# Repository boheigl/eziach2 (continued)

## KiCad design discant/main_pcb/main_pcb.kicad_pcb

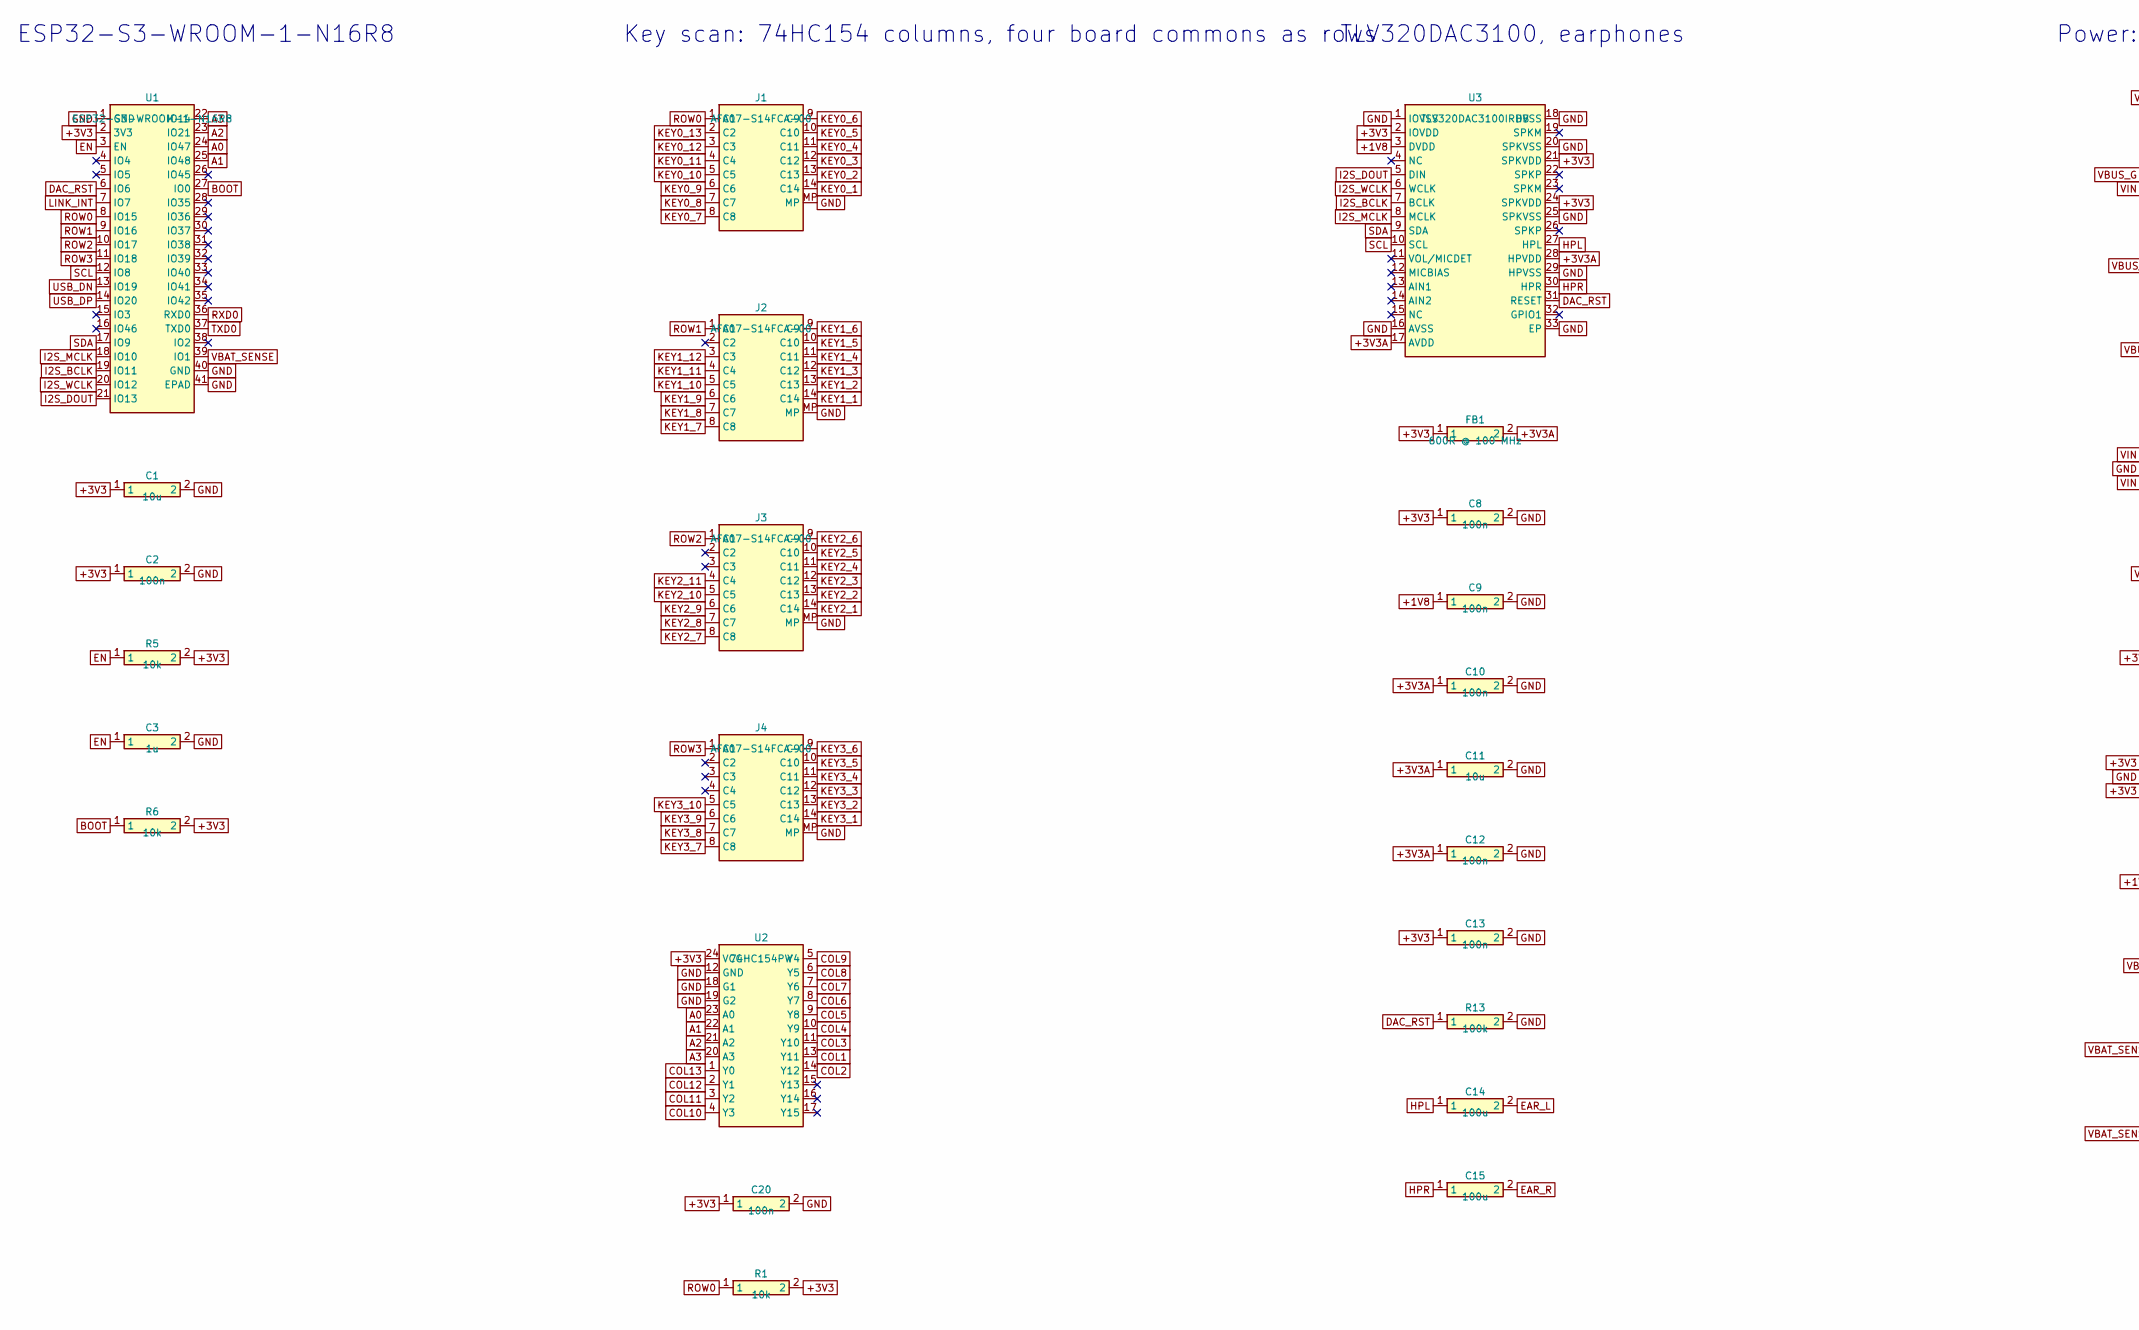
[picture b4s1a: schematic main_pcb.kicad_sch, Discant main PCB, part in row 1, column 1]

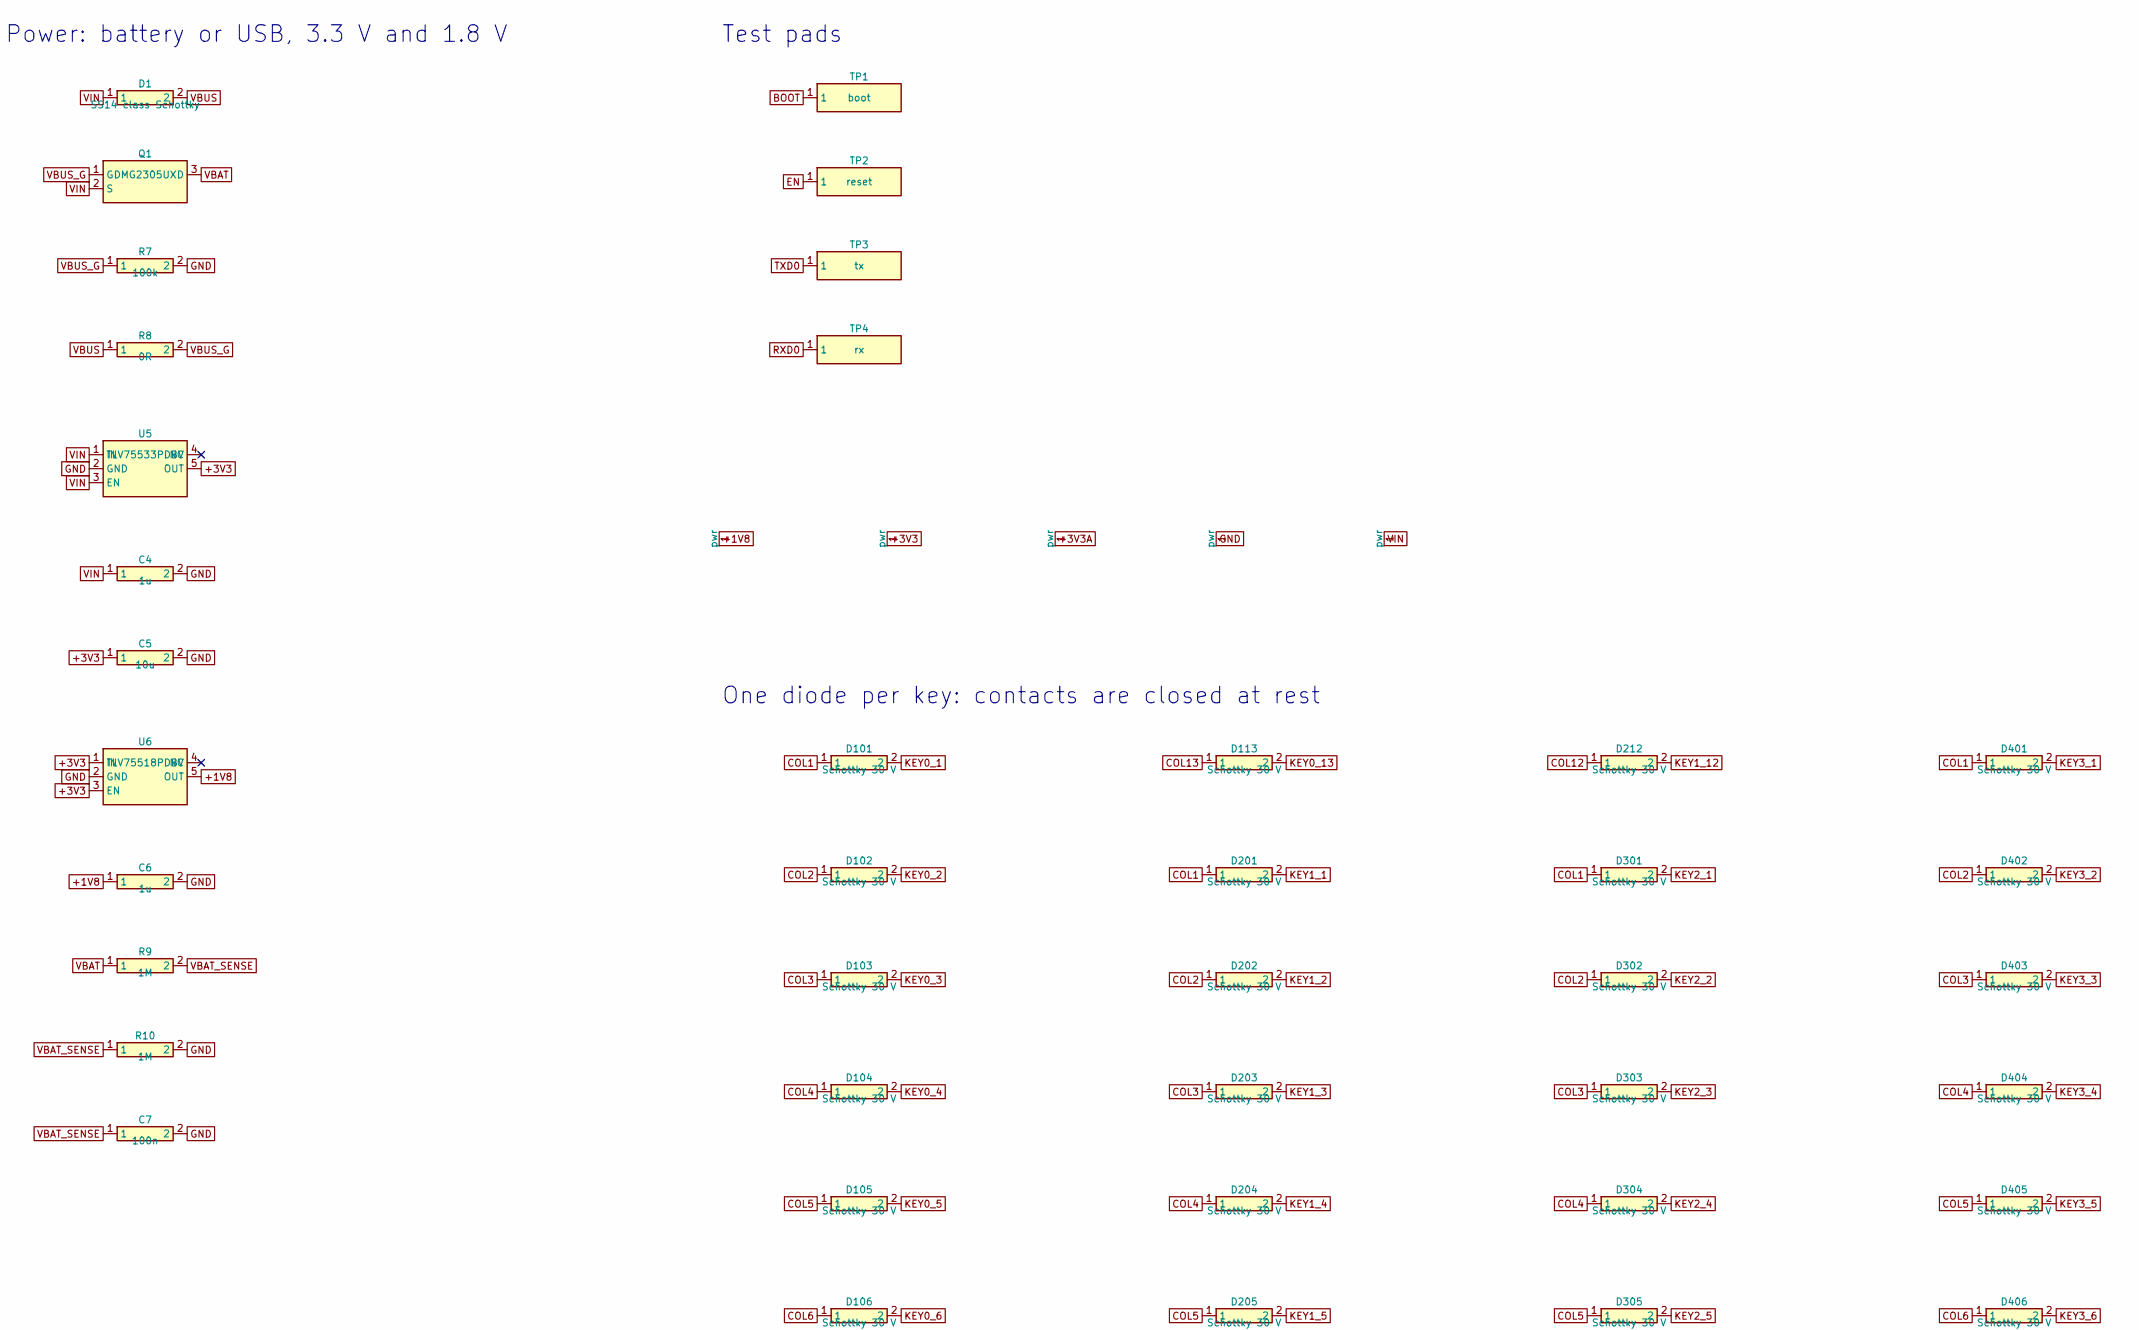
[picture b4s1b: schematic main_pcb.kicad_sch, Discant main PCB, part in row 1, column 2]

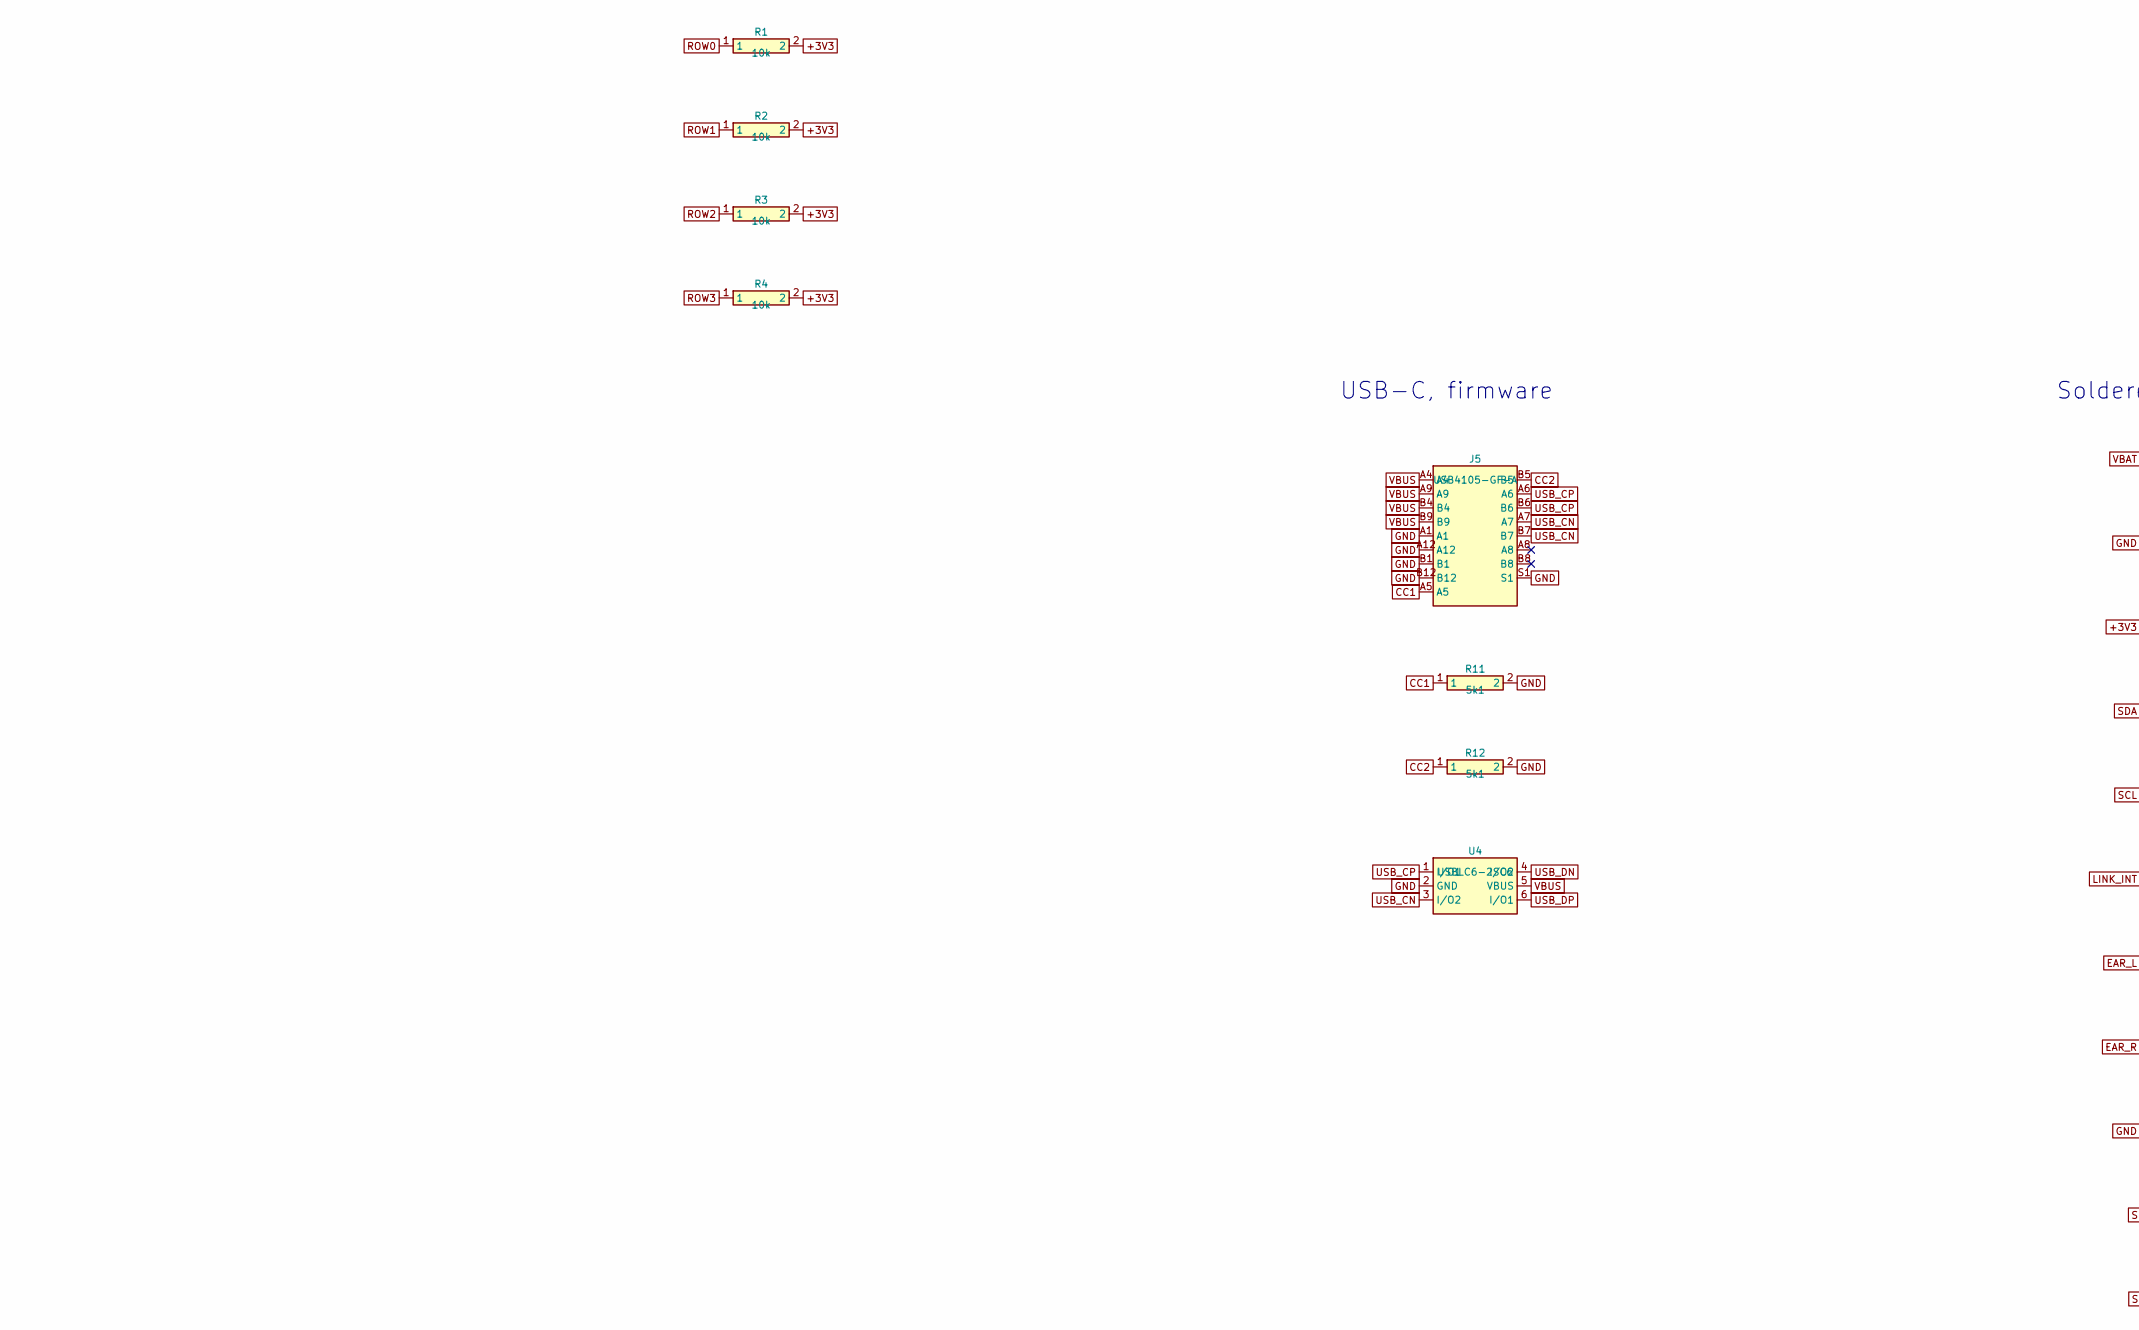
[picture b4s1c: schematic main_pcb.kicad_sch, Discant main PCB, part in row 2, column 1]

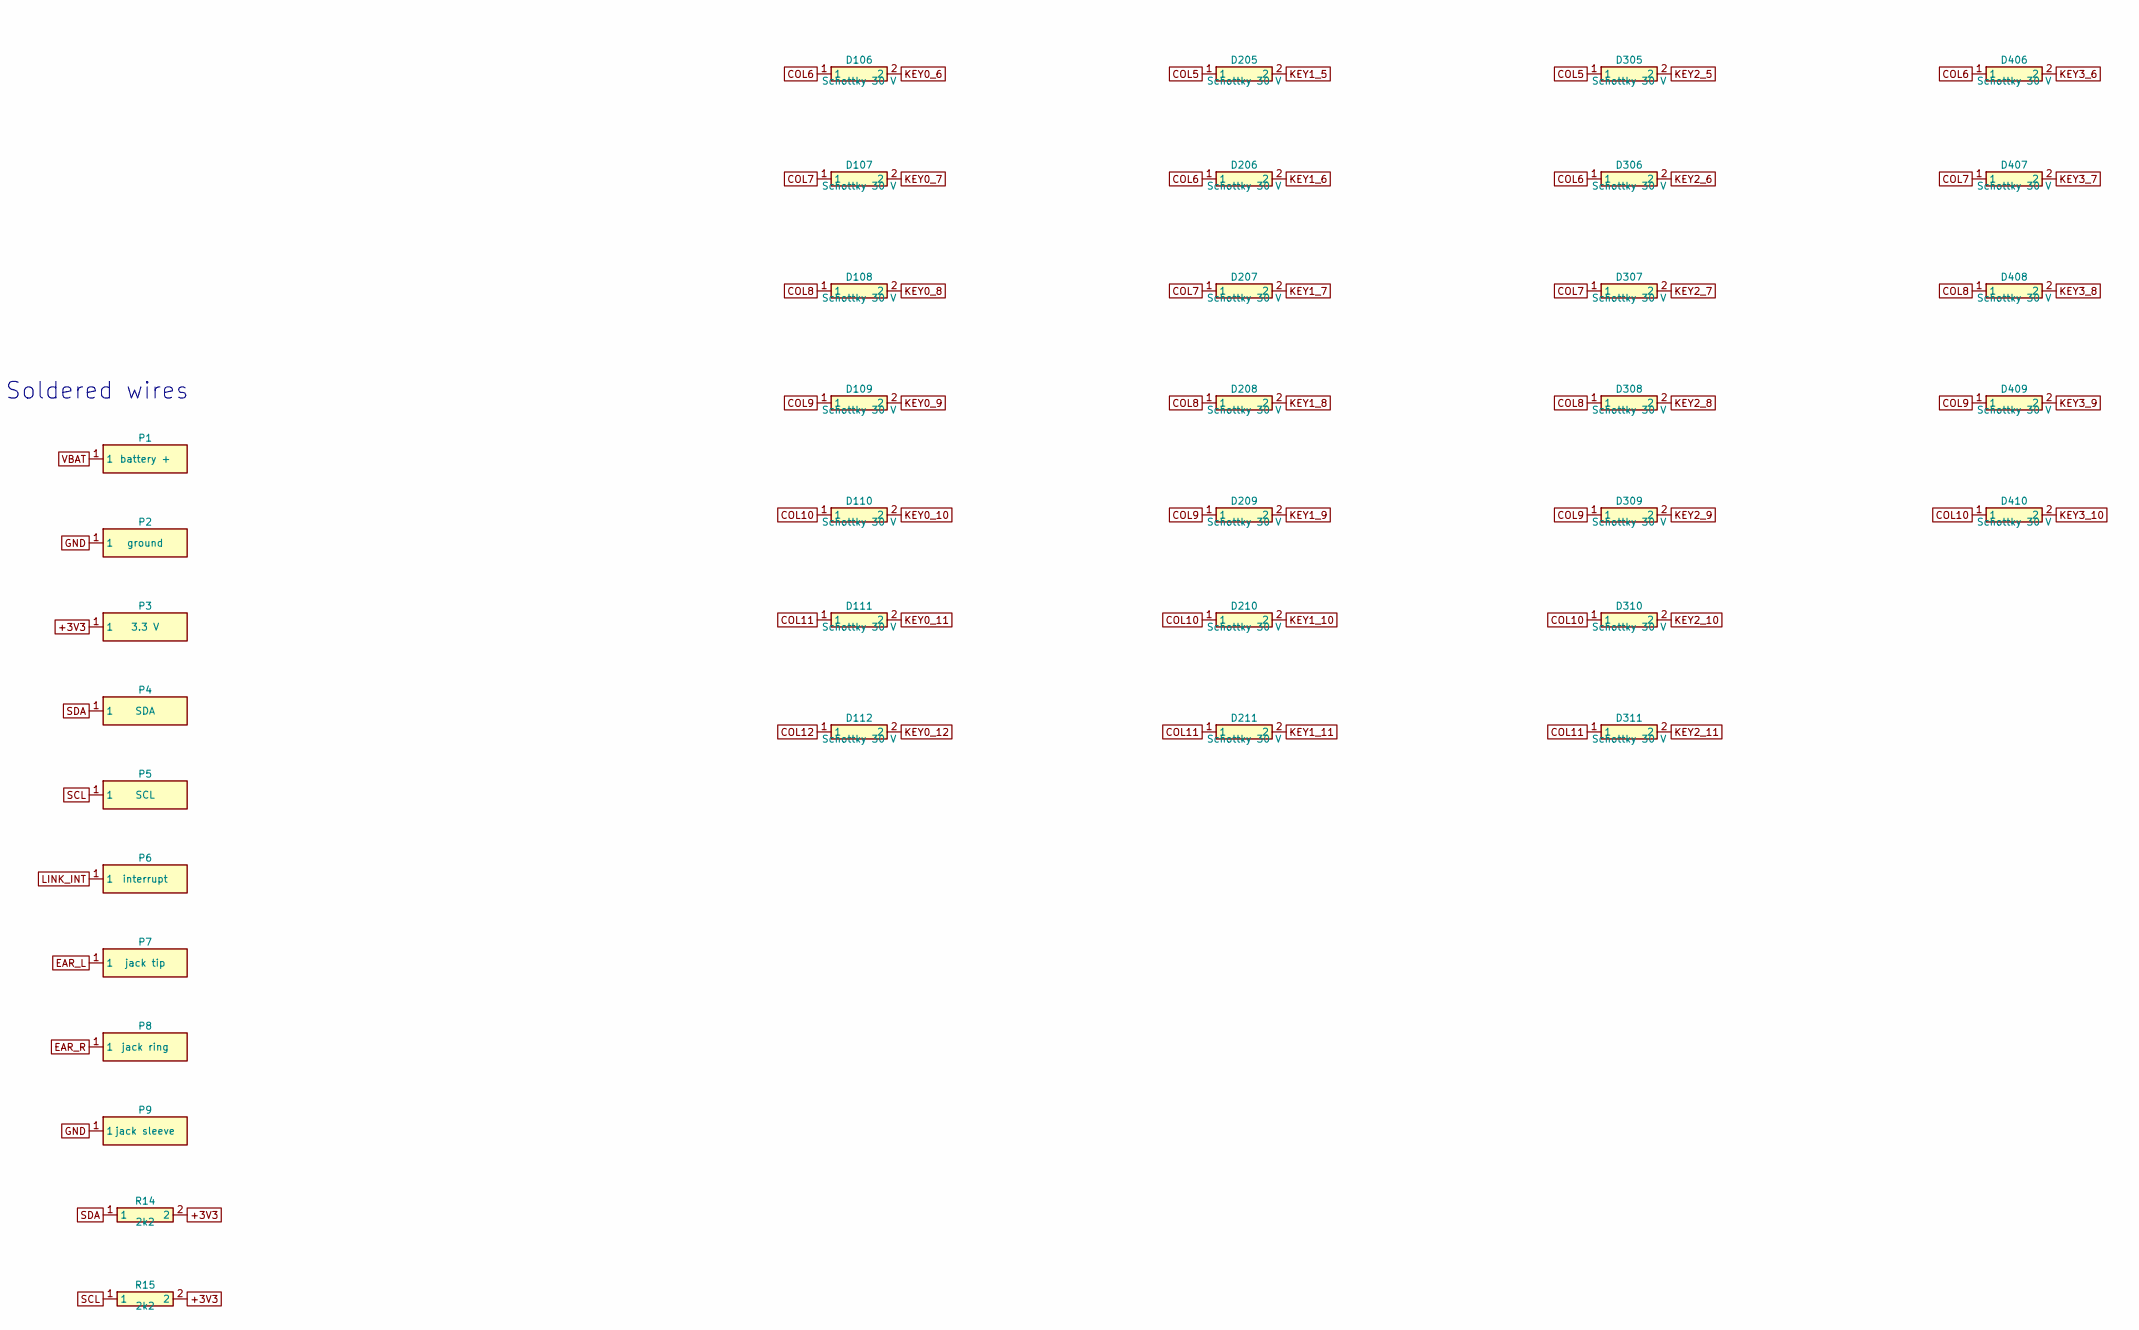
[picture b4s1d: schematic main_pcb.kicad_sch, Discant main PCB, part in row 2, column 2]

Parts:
C1, C5, C11: 10u; C_0603_1608Metric
C2, C7, C8, C9, C10, C12, C13, C20: 100n; C_0402_1005Metric
C3, C4, C6: 1u; C_0402_1005Metric
C14, C15: 100u; C_1206_3216Metric
D1: SS14 class Schottky; D_SOD-123
D101, D102, D103, D104, D105, D106, D107, D108, D109, D110, D111, D112, D113, D201, D202, D203, D204, D205, D206, D207, D208, D209, D210, D211, D212, D301, D302, D303, D304, D305, D306, D307, D308, D309, D310, D311, D401, D402, D403, D404, D405, D406, D407, D408, D409, D410: Schottky 30 V; D_SOD-882
FB1: 600R @ 100 MHz; L_0402_1005Metric
J1, J2, J3, J4: AFA07-S14FCA-00; JUSHUO_AFA07-S14FCA-00_1x14-1MP_P1.0mm_Horizontal
J5: USB4105-GF-A; USB_C_Receptacle_GCT_USB4105-xx-A_16P_TopMnt_Horizontal
P1: battery +; TestPoint_Pad_1.0x1.0mm
P2: ground; TestPoint_Pad_1.0x1.0mm
P3: 3.3 V; TestPoint_Pad_1.0x1.0mm
P4: SDA; TestPoint_Pad_1.0x1.0mm
P5: SCL; TestPoint_Pad_1.0x1.0mm
P6: interrupt; TestPoint_Pad_1.0x1.0mm
P7: jack tip; TestPoint_Pad_1.0x1.0mm
P8: jack ring; TestPoint_Pad_1.0x1.0mm
P9: jack sleeve; TestPoint_Pad_1.0x1.0mm
Q1: DMG2305UX; SOT-23
R1, R2, R3, R4, R5, R6: 10k; R_0402_1005Metric
R7, R13: 100k; R_0402_1005Metric
R8: 0R; R_0402_1005Metric
R9, R10: 1M; R_0402_1005Metric
R11, R12: 5k1; R_0402_1005Metric
R14, R15: 2k2; R_0402_1005Metric
TP1: boot; TestPoint_Pad_1.0x1.0mm
TP2: reset; TestPoint_Pad_1.0x1.0mm
TP3: tx; TestPoint_Pad_1.0x1.0mm
TP4: rx; TestPoint_Pad_1.0x1.0mm
U1: ESP32-S3-WROOM-1-N16R8; ESP32-S3-WROOM-1
U2: 74HC154PW; TSSOP-24_4.4x7.8mm_P0.65mm
U3: TLV320DAC3100IRHB; VQFN-32-1EP_5x5mm_P0.5mm_EP3.1x3.1mm
U4: USBLC6-2SC6; SOT-23-6
U5: TLV75533PDBV; SOT-23-5
U6: TLV75518PDBV; SOT-23-5

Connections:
+1V8: C6.1, C9.1, U3.3 (DVDD), U6.5 (OUT)
+3V3: C1.1, C2.1, C5.1, C8.1, C13.1, C20.1, FB1.1, P3.1, R1.2, R2.2, R3.2, R4.2, R5.2, R6.2, R14.2, R15.2, U1.2 (3V3), U2.24 (VCC), U3.2 (IOVDD), U3.21 (SPKVDD), U3.24 (SPKVDD), U5.5 (OUT), U6.1 (IN), U6.3 (EN)
+3V3A: C10.1, C11.1, C12.1, FB1.2, U3.17 (AVDD), U3.28 (HPVDD)
A0: U1.24 (IO47), U2.23 (A0)
A1: U1.25 (IO48), U2.22 (A1)
A2: U1.23 (IO21), U2.21 (A2)
A3: U1.22 (IO14), U2.20 (A3)
BOOT: R6.1, TP1.1, U1.27 (IO0)
CC1: J5.A5, R11.1
CC2: J5.B5, R12.1
COL1: D101.1, D201.1, D301.1, D401.1, U2.13 (Y11)
COL2: D102.1, D202.1, D302.1, D402.1, U2.14 (Y12)
COL3: D103.1, D203.1, D303.1, D403.1, U2.11 (Y10)
COL4: D104.1, D204.1, D304.1, D404.1, U2.10 (Y9)
COL5: D105.1, D205.1, D305.1, D405.1, U2.9 (Y8)
COL6: D106.1, D206.1, D306.1, D406.1, U2.8 (Y7)
COL7: D107.1, D207.1, D307.1, D407.1, U2.7 (Y6)
COL8: D108.1, D208.1, D308.1, D408.1, U2.6 (Y5)
COL9: D109.1, D209.1, D309.1, D409.1, U2.5 (Y4)
COL10: D110.1, D210.1, D310.1, D410.1, U2.4 (Y3)
COL11: D111.1, D211.1, D311.1, U2.3 (Y2)
COL12: D112.1, D212.1, U2.2 (Y1)
COL13: D113.1, U2.1 (Y0)
DAC_RST: R13.1, U1.6 (IO6), U3.31 (RESET)
EAR_L: C14.2, P7.1
EAR_R: C15.2, P8.1
EN: C3.1, R5.1, TP2.1, U1.3 (EN)
GND: C1.2, C2.2, C3.2, C4.2, C5.2, C6.2, C7.2, C8.2, C9.2, C10.2, C11.2, C12.2, C13.2, C20.2, J1.MP, J2.MP, J3.MP, J4.MP, J5.A1, J5.A12, J5.B1, J5.B12, J5.S1, P2.1, P9.1, R7.2, R10.2, R11.2, R12.2, R13.2, U1.1 (GND), U1.40 (GND), U1.41 (EPAD), U2.12 (GND), U2.18 (G1), U2.19 (G2), U3.1 (IOVSS), U3.16 (AVSS), U3.18 (DVSS), U3.20 (SPKVSS), U3.25 (SPKVSS), U3.29 (HPVSS), U3.33 (EP), U4.2 (GND), U5.2 (GND), U6.2 (GND)
HPL: C14.1, U3.27 (HPL)
HPR: C15.1, U3.30 (HPR)
I2S_BCLK: U1.19 (IO11), U3.7 (BCLK)
I2S_DOUT: U1.21 (IO13), U3.5 (DIN)
I2S_MCLK: U1.18 (IO10), U3.8 (MCLK)
I2S_WCLK: U1.20 (IO12), U3.6 (WCLK)
KEY0_1: D101.2, J1.14 (C14)
KEY0_2: D102.2, J1.13 (C13)
KEY0_3: D103.2, J1.12 (C12)
KEY0_4: D104.2, J1.11 (C11)
KEY0_5: D105.2, J1.10 (C10)
KEY0_6: D106.2, J1.9 (C9)
KEY0_7: D107.2, J1.8 (C8)
KEY0_8: D108.2, J1.7 (C7)
KEY0_9: D109.2, J1.6 (C6)
KEY0_10: D110.2, J1.5 (C5)
KEY0_11: D111.2, J1.4 (C4)
KEY0_12: D112.2, J1.3 (C3)
KEY0_13: D113.2, J1.2 (C2)
KEY1_1: D201.2, J2.14 (C14)
KEY1_2: D202.2, J2.13 (C13)
KEY1_3: D203.2, J2.12 (C12)
KEY1_4: D204.2, J2.11 (C11)
KEY1_5: D205.2, J2.10 (C10)
KEY1_6: D206.2, J2.9 (C9)
KEY1_7: D207.2, J2.8 (C8)
KEY1_8: D208.2, J2.7 (C7)
KEY1_9: D209.2, J2.6 (C6)
KEY1_10: D210.2, J2.5 (C5)
KEY1_11: D211.2, J2.4 (C4)
KEY1_12: D212.2, J2.3 (C3)
KEY2_1: D301.2, J3.14 (C14)
KEY2_2: D302.2, J3.13 (C13)
KEY2_3: D303.2, J3.12 (C12)
KEY2_4: D304.2, J3.11 (C11)
KEY2_5: D305.2, J3.10 (C10)
KEY2_6: D306.2, J3.9 (C9)
KEY2_7: D307.2, J3.8 (C8)
KEY2_8: D308.2, J3.7 (C7)
KEY2_9: D309.2, J3.6 (C6)
KEY2_10: D310.2, J3.5 (C5)
KEY2_11: D311.2, J3.4 (C4)
KEY3_1: D401.2, J4.14 (C14)
KEY3_2: D402.2, J4.13 (C13)
KEY3_3: D403.2, J4.12 (C12)
KEY3_4: D404.2, J4.11 (C11)
KEY3_5: D405.2, J4.10 (C10)
KEY3_6: D406.2, J4.9 (C9)
KEY3_7: D407.2, J4.8 (C8)
KEY3_8: D408.2, J4.7 (C7)
KEY3_9: D409.2, J4.6 (C6)
KEY3_10: D410.2, J4.5 (C5)
LINK_INT: P6.1, U1.7 (IO7)
ROW0: J1.1 (C1), R1.1, U1.8 (IO15)
ROW1: J2.1 (C1), R2.1, U1.9 (IO16)
ROW2: J3.1 (C1), R3.1, U1.10 (IO17)
ROW3: J4.1 (C1), R4.1, U1.11 (IO18)
RXD0: TP4.1, U1.36 (RXD0)
SCL: P5.1, R15.1, U1.12 (IO8), U3.10 (SCL)
SDA: P4.1, R14.1, U1.17 (IO9), U3.9 (SDA)
TXD0: TP3.1, U1.37 (TXD0)
USB_CN: J5.A7, J5.B7, U4.3 (I/O2)
USB_CP: J5.A6, J5.B6, U4.1 (I/O1)
USB_DN: U1.13 (IO19), U4.4 (I/O2)
USB_DP: U1.14 (IO20), U4.6 (I/O1)
VBAT: P1.1, Q1.3 (D), R9.1
VBAT_SENSE: C7.1, R9.2, R10.1, U1.39 (IO1)
VBUS: D1.2, J5.A4, J5.A9, J5.B4, J5.B9, R8.1, U4.5 (VBUS)
VBUS_G: Q1.1 (G), R7.1, R8.2
VIN: C4.1, D1.1, Q1.2 (S), U5.1 (IN), U5.3 (EN)

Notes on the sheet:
ESP32-S3-WROOM-1-N16R8
Key scan: 74HC154 columns, four board commons as rows
TLV320DAC3100, earphones
USB-C, firmware
Power: battery or USB, 3.3 V and 1.8 V
Soldered wires
Test pads
One diode per key: contacts are closed at rest

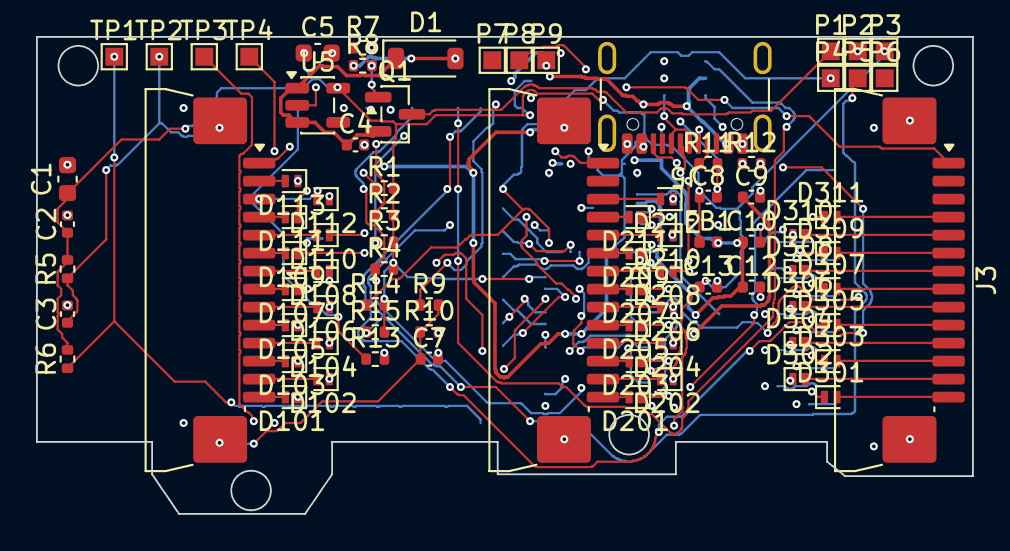
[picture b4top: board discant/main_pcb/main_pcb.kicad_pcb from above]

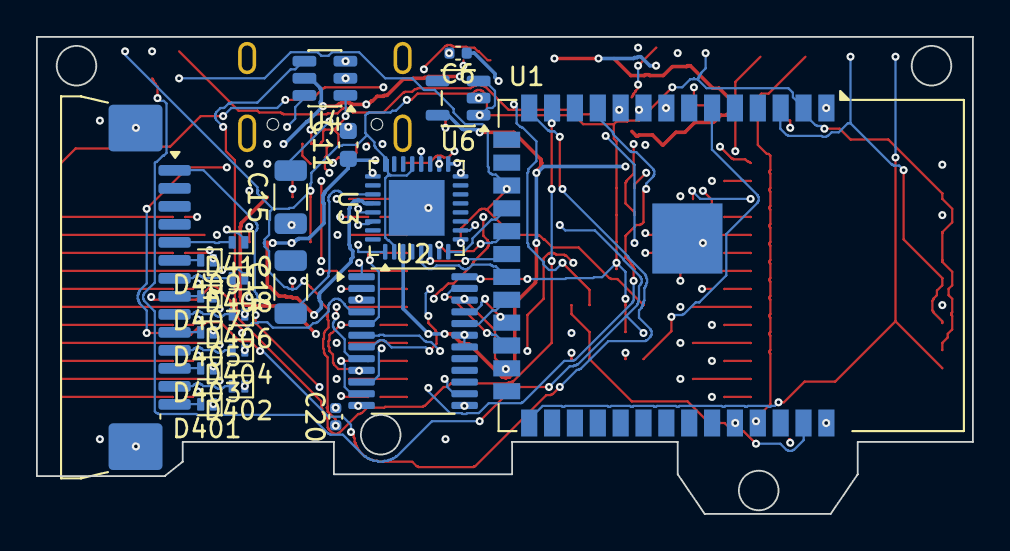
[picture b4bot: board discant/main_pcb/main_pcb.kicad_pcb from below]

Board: 4 copper layers, 52.0 x 26.5 mm, 104 parts (21 on the bottom side), 98 nets.

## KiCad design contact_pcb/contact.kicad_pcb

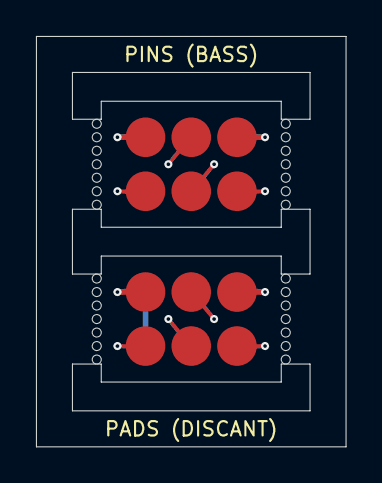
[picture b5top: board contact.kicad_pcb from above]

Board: 2 copper layers, 17.2 x 22.8 mm, 6 parts (0 on the bottom side), 11 nets.

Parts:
J1, J2: PG2541-03-003P
K1: contact pads
MB: mouse bites
W1, W2: wire pads

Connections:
B_3V3: J1.1, W1.1
B_DET: J2.3, W1.6
B_GND: J1.3, W1.3
B_INT: J2.1, W1.4
B_SCL: J1.2, W1.2
B_SDA: J2.2, W1.5
D_3V3: K1.1, W2.1
D_GND: K1.3, K1.6, W2.3, W2.6
D_INT: K1.4, W2.4
D_SCL: K1.2, W2.2
D_SDA: K1.5, W2.5

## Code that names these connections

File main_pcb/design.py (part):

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       "9": "CHG", "10": "VSYS", "11": "VSYS", "12": "ILIM", "13": "VBUS", "14": "TMR", "15": None,
       "16": "ISET", "17": "GND"}
part("U3", "BQ24074RGTR", "Package_DFN_QFN:VQFN-16-1EP_3x3mm_P0.5mm_EP1.6x1.6mm", chg, (12.9, 21.3, 0),
     pinfo={"1": "TS", "2": "BAT", "3": "BAT", "4": "~CE", "5": "EN2", "6": "EN1", "7": "~PGOOD", "8": "VSS",
            "9": "~CHG", "10": "OUT", "11": "OUT", "12": "ILIM", "13": "IN", "14": "TMR", "15": "ITERM",
            "16": "ISET", "17": "VSS"}, group="charger", title="Charger")
Cc("C4", "4u7", "VBUS", "GND", (12.9, 24.9, 0), "charger", C0603)
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#        up through the red LED and R9 once ~CHG lets go, so green comes on when the
#        charge is done and red goes off. Without USB ~PGOOD is open: no green.
part("D1", "LTST-S326KGJRKT", "LED_SMD:LED_LiteOn_LTST-S326",
     {"1": "LED_R", "2": "LED_G", "3": "VSYS"}, (None, 29.0, None), pinfo={"1": "C1 (K red)", "2": "C2 (K green)", "3": "A"},
     group="charger")
R("R9", "1k5", "LED_R", "CHG", (3.4, 27.4, 0), "charger")
part("Q4", "DMG1012T", "Package_TO_SOT_SMD:SOT-523", {"1": "CHG", "2": "PGOOD", "3": "LED_GQ"}, (8.4, 25.85, 90),
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# fixed frequency, no power-save bursts near the audio
part("U5", "TPS63001DRCR", "Package_SON:Texas_DRC0010J", {"1": "+3V3", "2": "L2", "3": "GND", "4": "L1",
     "5": "VSYS", "6": "EN_SYS", "7": "VSYS", "8": "VINA", "9": "GND", "10": "+3V3", "11": "GND"}, (19.8, 21.3, 180),
     pinfo={"1": "VOUT", "2": "L2", "3": "PGND", "4": "L1", "5": "VIN", "6": "EN", "7": "PS/SYNC", "8": "VINA",
            "9": "GND", "10": "FB", "11": "PGND"}, group="power", title="3.3 V")
# Its power loop as SLVS520C 8.2.2.3 asks [review/main_pcb.md, 2026-11-18]: U5 turned so
# its power pins (VOUT, L2, PGND, L1, VIN) face +X; the inductor upright beside L1/L2, the
# input cap at VIN above, the output caps at VOUT below, their GND ends at the
# exposed pad; the VINA filter on the other side, at pin 8
part("L1", "2.2u, Isat 2 A", "Inductor_SMD:L_1008_2520Metric", {"1": "L1", "2": "L2"}, (23.2, 21.3, 270), group="power")
Cc("C10", "10u", "VSYS", "GND", (21.0, 24.3, 180), "power", C0805)
R("R17", "100R", "VSYS", "VINA", (18.2, 24.3, 0), "power")
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       "14": (None, "AIN2"), "15": (None, "NC"), "16": ("GND", "AVSS"), "17": ("+3V3A", "AVDD"), "18": ("GND", "DVSS"),
       "19": (None, "SPKM"), "20": ("GND", "SPKVSS"), "21": ("+3V3", "SPKVDD"), "22": (None, "SPKP"), "23": (None, "SPKM"),
       "24": ("+3V3", "SPKVDD"), "25": ("GND", "SPKVSS"), "26": (None, "SPKP"), "27": ("HPL", "HPL"), "28": ("+3V3A", "HPVDD"),
       "29": ("GND", "HPVSS"), "30": ("HPR", "HPR"), "31": ("DAC_RST", "RESET"), "32": (None, "GPIO1"), "33": ("GND", "EP")}
part("U7", "TLV320DAC3100IRHBR", "Package_DFN_QFN:VQFN-32-1EP_5x5mm_P0.5mm_EP3.1x3.1mm",
     {p: v[0] for p, v in dac.items()}, (36.4, 29.8, 90), pinfo={p: v[1] for p, v in dac.items()}, group="audio",
     title="Audio")
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
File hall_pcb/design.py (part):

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    for p in ADC_AIN: pins[p] = None
    part(f"U{a + 1}", "ADS7128IRTER", WQFN16, pins, (x, ADC_Y[a]), group="adc",
         title=f"ADC {a}, address {0x10 + a:02X}h",
         pinfo={**{p: f"AIN{c}" for p, c in ADC_AIN.items()}, "7": "AVDD", "8": "DECAP", "9": "GND",
                "10": "DVDD", "11": "ADDR", "12": "ALERT", "13": "SCL", "14": "SDA", "17": "EP"})
    part(f"C{10 * a + 11}", "1u", C0402, {"1": "+3V3", "2": "GND"}, group="adc")       # AVDD
    part(f"C{10 * a + 12}", "1u", C0402, {"1": f"DECAP{a}", "2": "GND"}, group="adc")  # DECAP
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           "15": "+3V3", "16": "AVDD"}
    part("U7", "NAU7802SGI", SOIC16, NAU, (0.0, 49.4), rot=NAU_ROT,
         group="gauge", title="Gauges' ADC NAU7802, address 2Ah",
         pinfo={"1": "REFP", "2": "VIN1N", "3": "VIN1P", "4": "VIN2N", "5": "VIN2P", "6": "VBG", "7": "REFN",
                "8": "AVSS", "9": "DVSS", "10": "XIN", "11": "XOUT", "12": "DRDY", "13": "SCLK", "14": "SDIO",
                "15": "DVDD", "16": "AVDD"})
    part("FB1", "600R @ 100 MHz", L0402, {"1": "+3V3", "2": "AVDD"}, (-7.0, 43.6), rot=0, group="gauge")
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    part("C6", "100n", C0402, {"1": "VBG", "2": "GND"}, (6.6, 48.6), rot=90, group="gauge")
    for k, (gx, s) in enumerate([(-12.0, -1), (12.0, 1)]):
        n = k + 1
        part(f"J{n + 1}", f"gauge {'AB'[k]}", WIRE3, {"1": "AVDD", "2": f"G{n}", "3": "GND"}, (gx + 2.0, WIRE_Y), rot=90,
             group="gauge", pinfo={"1": "E+", "2": "MID", "3": "E-"})
        part(f"R{20 + 6 * k + 1}", "10k 0.1%", R0402, {"1": "AVDD", "2": f"GREF{n}"}, (s * 16.0, 51.2), group="gauge")
        part(f"R{20 + 6 * k + 2}", "10k 0.1%", R0402, {"1": f"GREF{n}", "2": "GND"}, (s * 16.0, 52.5), group="gauge")
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
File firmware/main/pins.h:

/* eziach - electrical accordion
 *
 * Copyright (C) 2026  Benno Heigl
 *
 * This library is free software; you can redistribute it and/or
 * modify it under the terms of the GNU Lesser General Public License
 * as published by the Free Software Foundation; either version 2.1 of
 * the License, or (at your option) any later version.
 *
 * This library is distributed in the hope that it will be useful, but
 * WITHOUT ANY WARRANTY; without even the implied warranty of
 * MERCHANTABILITY or FITNESS FOR A PARTICULAR PURPOSE.  See the GNU
 * Lesser General Public License for more details.
 *
 * You should have received a copy of the GNU Lesser General Public
 * License along with this library; if not, see
 * <https://www.gnu.org/licenses/>.
 */

// The ESP32-S3's pins on the main board (../main_pcb/spec.md, I/O table).

#ifndef PINS_H
#define PINS_H

// I2C bus 1, through the contacts: the discant's ADCs 10h-15h and the gauges' NAU7802 (2Ah)
#define PIN_SDA1 13
#define PIN_SCL1 14
#define PIN_INT1 21
// I2C bus 2, in the bass: the bass's ADCs 10h-12h and the DAC (18h)
#define PIN_SDA2 47
#define PIN_SCL2 48
#define PIN_INT2 38
// I2S to the DAC [2026-11-19: one module pin to the right, in the DAC's pin order, so the
// four lines run straight down to it; SDA1 took IO13]
#define PIN_MCLK 9
#define PIN_BCLK 10
#define PIN_WCLK 11
#define PIN_DOUT 12
// others
#define PIN_DAC_RESET 39     // low: DAC in reset
#define PIN_DISCANT_ON 40    // the discant's 3.3 V through 10k / 100k: high when it is plugged
#define PIN_VBUS 41          // USB's 5 V through 68k / 100k
#define PIN_CC1 2            // USB-C CC1 and CC2 (ADC1 channels 1 and 3): what the source offers
#define PIN_CC2 4
#define PIN_CHG_EN1 5        // the charger's EN1 / EN2: 500 mA (low/high by pulls) or 1 A by ILIM (high/low)
#define PIN_CHG_EN2 6
#define PIN_VBAT 1           // the cell through 1M / 1M (ADC1 channel 0)
#define PIN_LOW_BAT 42       // high: the red low-battery light

#define I2C_FREQ_HZ 400000   // ../hall_pcb/spec.md: rise times checked for 400 kHz

#endif
